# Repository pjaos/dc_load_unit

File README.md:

# DC Load Unit
I started this project with some basic requirements.

- Voltages up to 100 V
- Provide loads of up to 200W
- WiFi interface
- Web based interface providing stats and plotting capabilities

## Design
I used an ESP32 processor in the design as the main processor using  [Mongoose OS](https://mongoose-os.com/) After some investigations and prototyping I eventually settled on the schematic shown below.

From the schematic a PCB was created as shown below

Tests on completion of the load unit showed it was capable of providing a load of 280W.

- Images of the completed unit.

The green LED on the unit indicates that it is connected to the WiFi.

## Web interface
The web interface uses a tabbed pane structure as shown below.

### Main interface

- Plots
The plots tab displays the amps, volts, Watts and Temperature against time as show below.

- Load stats
The load stats page records the load in amp hours and watt hours. The top two dials show the current accumulating values and the bottom two dials show the previous values. The previous values are useful for showing the total capacity of a battery tested.

- Configuration
The configuration page details the settings for the unit as detailed below.

- Device name:

 The name that appears at the top of the web page and also in the [Yview](https://github.com/pjaos/yview) as the device provides integration into the YView network.

- Group name:

  The YView group name. See [Yview](https://github.com/pjaos/yview) for more details.

- Enable syslog

  If enabled then syslog data is sent to the source of the AYT messages (YView gateway).

- Max Plot values

  Defines the max number of points on the displayed plots.

- Max power

  This defines the maximum power the load will handle. This is limited to 280 Watts. When testing it can be useful to set this value to the max load that the device under test will deliver in order not to inadvertently overload the device under test.

- Load Shutdown Voltage

  When testing battery packs the voltage will drop as the battery looses charge. This setting allows the user to ensure the battery voltage does not drop to far possibly damaging the battery.

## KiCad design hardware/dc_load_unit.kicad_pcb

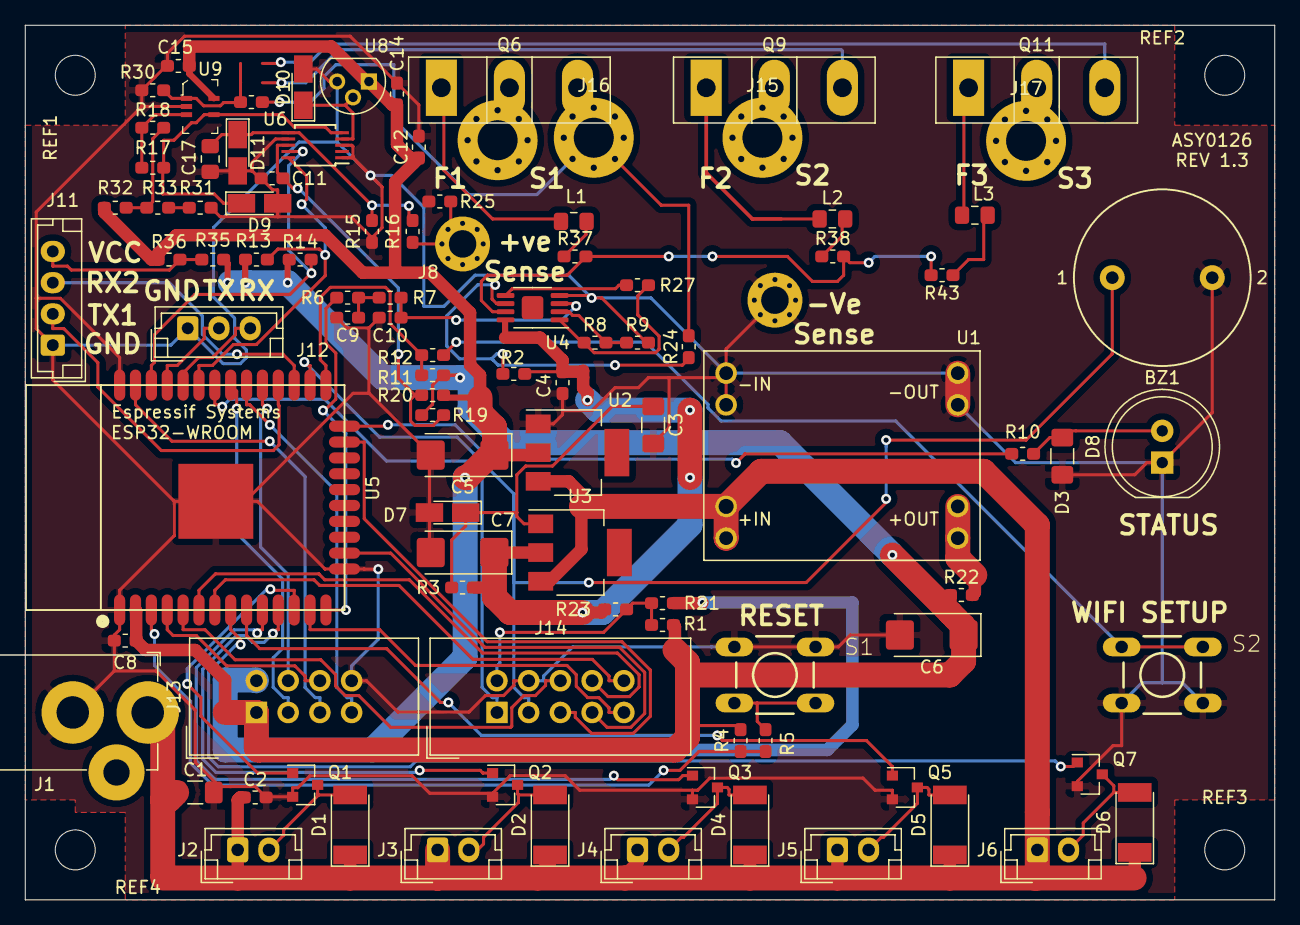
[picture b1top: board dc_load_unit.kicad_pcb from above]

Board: 2 copper layers, 100.0 x 70.0 mm, 104 parts (0 on the bottom side), 71 nets.

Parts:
BZ1: Buzzer; Buzzer_14mm_8mm_pitch
C1: 10uf 25v; C_1206_3216Metric_Pad1.42x1.75mm_HandSolder
C2, C4, C8: 0.1uf; C_0603_1608Metric_Pad1.05x0.95mm_HandSolder
C3: 10uf; C_1206_3216Metric_Pad1.42x1.75mm_HandSolder
C5, C6, C7: 22uf; CP_EIA-6032-20_AVX-F_Pad2.25x2.35mm_HandSolder
C9: 4.7nf; C_0603_1608Metric_Pad1.05x0.95mm_HandSolder
C10: 8.2nf; C_0603_1608Metric_Pad1.05x0.95mm_HandSolder
C11, C12, C14, C15: .1uf; C_0603_1608Metric_Pad1.05x0.95mm_HandSolder
C17: 470nf; C_0805_2012Metric_Pad1.15x1.40mm_HandSolder
D1, D2, D4, D5, D6: 1N4004; D_MELF
D3: LED; C_1206_3216Metric_Pad1.42x1.75mm_HandSolder
D7: 4V7; D_MicroMELF_Hadsoldering
D8: LED; LED_D8.0mm
D9, D10, D11: 3V; D_MicroMELF_Hadsoldering
J1: Conn_01x02_Male; DC_power_2.1mm_5.5mm
J2, J3, J4, J5, J6: Conn_01x02_Female; JST_EH_B2B-EH-A_1x02_P2.50mm_Vertical
J7: -Ve Sense; MountingHole_2.2mm_M2_Pad_Via
J8: +Ve Sense; MountingHole_2.2mm_M2_Pad_Via
J9: To Fuse 1; MountingHole_3.2mm_M3_Pad_Via
J11: Conn_01x04; JST_EH_B4B-EH-A_1x04_P2.50mm_Vertical
J12: Conn_01x03_Male; JST_EH_B3B-EH-A_1x03_P2.50mm_Vertical
J13: Conn_02x04_Odd_Even; IDC-Header_2x04_P2.54mm_Vertical
J14: Conn_02x05_Odd_Even; IDC-Header_2x05_P2.54mm_Vertical
J15: To Fuse 2; MountingHole_3.2mm_M3_Pad_Via
J16: 0.22R Shunt; MountingHole_3.2mm_M3_Pad_Via
J17: To Fuse 3; MountingHole_3.2mm_M3_Pad_Via
L1, L2, L3: 2.2uh; L_0805_2012Metric_Pad1.15x1.40mm_HandSolder
Q1, Q2, Q3, Q5, Q7: 2N7002; SOT-23
Q6, Q9, Q11: IXFH80N25X3; TO-247-3_Vertical
R1, R19, R22, R35: R0; R_0603_1608Metric_Pad1.05x0.95mm_HandSolder
R2: 150k; R_0603_1608Metric_Pad1.05x0.95mm_HandSolder
R3, R5, R12, R15: 470R; R_0603_1608Metric_Pad1.05x0.95mm_HandSolder
R4: 12k; R_0603_1608Metric_Pad1.05x0.95mm_HandSolder
R6, R7, R9: 10k; R_0603_1608Metric_Pad1.05x0.95mm_HandSolder
R8: 2.2k; R_0603_1608Metric_Pad1.05x0.95mm_HandSolder
R10: 681R; R_0603_1608Metric_Pad1.05x0.95mm_HandSolder
R11: 12K; R_0603_1608Metric_Pad1.05x0.95mm_HandSolder
R13, R14: 4k7; R_0603_1608Metric_Pad1.05x0.95mm_HandSolder
R16, R34: 33k; R_0603_1608Metric_Pad1.05x0.95mm_HandSolder
R17, R18, R25: 100k; R_0603_1608Metric_Pad1.05x0.95mm_HandSolder
R20, R21, R23, R32, R36: DNF; R_0603_1608Metric_Pad1.05x0.95mm_HandSolder
R24: 100R; R_0603_1608Metric_Pad1.05x0.95mm_HandSolder
R27, R33: 0R; R_0603_1608Metric_Pad1.05x0.95mm_HandSolder
R30: 68k; R_0603_1608Metric_Pad1.05x0.95mm_HandSolder
R31: 1k; R_0603_1608Metric_Pad1.05x0.95mm_HandSolder
R37, R38, R43: 2k2; R_0603_1608Metric_Pad1.05x0.95mm_HandSolder
REF1, REF2, REF3, REF4: MountingHole_3.2mm_M3
S1, S2: DTS-6; switch-tact-DTS-6
U1: DC_DC_MODULE_8_PIN; mp1584_dc_dc
U2, U3: LM1117-5V; SOT-223
U4: LM358; MSOP-8-1EP_3x3mm_P0.65mm_EP1.73x1.85mm
U5: ESP32-WROOM
U6: ADS1115IDGS; TSSOP-10_3x3mm_P0.5mm
U8: MCP9700; TO-92
U9: MCP6241UT-E_LT; SC-70-5

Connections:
3V3: C6.1, C8.1, J13.1, R1.1, R4.1, R11.2, R13.1, R14.1, R19.2, R22.1, R35.1, U5.2
5V: C5.1, C12.1, C14.1, C15.1, J13.2, R20.1, R21.1, R32.2, R36.1, U2.2, U8.1, U9.5
9V7: C4.1, C7.1, R2.1, R3.2, R23.1, U3.2, U4.8
12V: C1.1, C2.1, D1.1, D2.1, D4.1, D5.1, D6.1, J1.1, J2.1, J3.1, J4.1, J5.1, J6.1, U1.3, U1.4, U2.3, U3.3
/High_Power/+veSense: J8.1, R16.2, R25.1
/High_Power/GateDrive: R37.2, R38.2, R43.2, U4.7
/High_Power/Shunt: J16.1, Q6.3, Q9.3, Q11.3, R24.2, R34.2
CLK: J13.7, U5.30
CS: J13.4, U5.29
F1: Q1.1, U5.12
F2: Q2.1, U5.11
F3: Q3.1, U5.10
F4: Q5.1, U5.9
F5: Q7.1, U5.8
GND: BZ1.2, C1.2, C2.2, C3.2, C4.2, C5.2, C6.2, C7.2, C8.2, C9.2, C10.2, C11.2, C12.2, C14.2, C15.2, C17.2, D3.1, D7.2, D8.1, D9.2, D10.2, D11.2, J1.2, J7.1, J11.1, J12.1, J13.8, J14.4, Q1.2, Q2.2, Q3.2, Q5.2, Q7.2, R9.2, R15.2, R25.2, R30.2, R31.1, S1.1, S1.2, S2.1, S2.2, U1.1, U1.2, U1.5, U1.6, U2.1, U4.4, U5.1, U5.15, U5.38, U5.39, U6.1, U6.3, U6.7, U8.3, U9.2
INT: J13.6, U5.4
IO0: R11.1, R12.2, U5.25
MISO: J13.3, U5.31
MOSI: J13.5, U5.37
unnamed: C3.1, D7.1, R3.1, U3.1
unnamed: C9.1, R6.1, R7.2
unnamed: C10.1, R7.1, U4.3
unnamed: C11.1, R19.1, R20.2, U6.8
unnamed: C17.1, D11.1, R15.1, R16.1, U6.6
unnamed: D1.2, J2.2, Q1.3
unnamed: D2.2, J3.2, Q2.3
unnamed: D3.2, D8.2, R10.1
unnamed: D4.2, J4.2, Q3.3
unnamed: D5.2, J5.2, Q5.3
unnamed: D6.2, J6.2, Q7.3
unnamed: D9.1, R17.1, U6.5, U9.4
unnamed: D10.1, U6.4, U8.2
unnamed: J9.1, Q6.2
unnamed: J11.4, R35.2, R36.2
unnamed: J14.2, R1.2, R21.2, R23.2
unnamed: J15.1, Q9.2
unnamed: J17.1, Q11.2
unnamed: L1.1, R37.1
unnamed: L1.2, Q6.1
unnamed: L2.1, R38.1
unnamed: L2.2, Q9.1
unnamed: L3.1, R43.1
unnamed: L3.2, Q11.1
unnamed: R2.2, R24.1, U4.6
unnamed: R4.2, R5.1, U5.3
unnamed: R5.2, S1.3, S1.4
unnamed: R6.2, U5.14
unnamed: R8.2, R9.1, U4.2
unnamed: R10.2, U5.24
unnamed: R12.1, S2.3, S2.4
unnamed: R13.2, U5.33, U6.10
unnamed: R14.2, U5.36, U6.9
unnamed: R17.2, R18.1, U9.3
unnamed: R18.2, R32.1, R33.2
unnamed: R22.2, U1.7, U1.8
unnamed: R27.1, U4.5
unnamed: R8.1, R27.2, U4.1
unnamed: R30.1, R34.1, U9.1
unnamed: R31.2, R33.1
RXD: J12.3, U5.34
RXD2: J11.3, U5.27
SP1: J14.1, U5.32
SP2: BZ1.1, J14.3, U5.26
SP3: J14.5, U5.23
SP4: J14.7, U5.16
SP5: J14.9, U5.13
SP6: J14.10, U5.7
SP7: J14.8, U5.6
SP8: J14.6, U5.5
TXD: J12.2, U5.35
TXD2: J11.2, U5.28

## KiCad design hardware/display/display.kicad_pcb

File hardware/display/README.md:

# Display board
This was a side project of an LCD display board that could be used with the
dc load unit to control it. However the web interface is my preferred
GUI interface and therefore I did not develop this board any further.

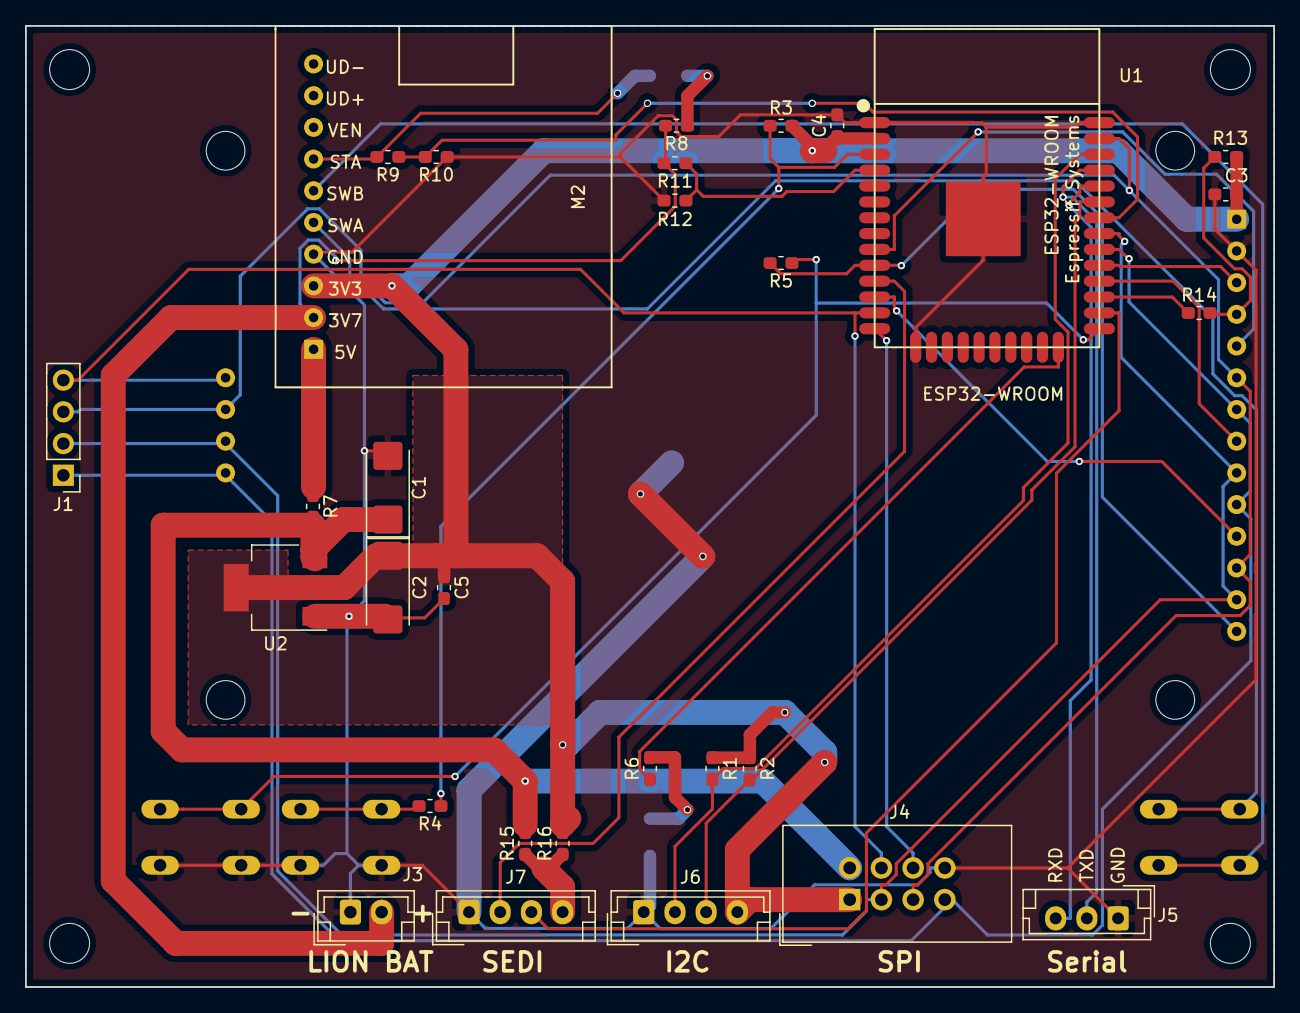
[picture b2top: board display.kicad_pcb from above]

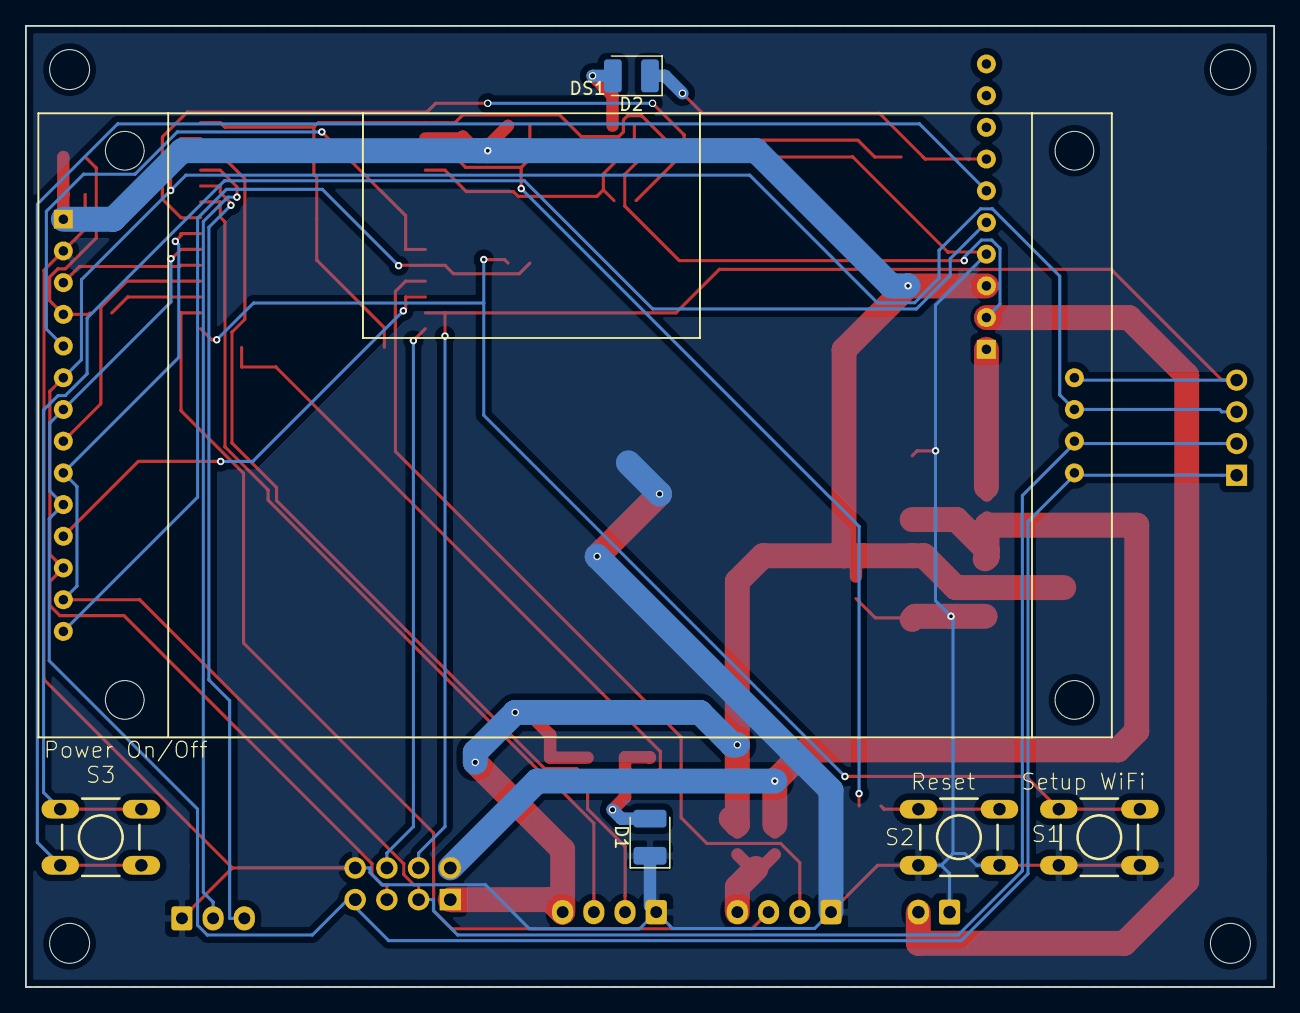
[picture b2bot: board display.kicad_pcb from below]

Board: 2 copper layers, 100.0 x 77.0 mm, 40 parts (6 on the bottom side), 35 nets.

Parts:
C1, C2: DNF; CP_EIA-6032-20_AVX-F_Pad2.25x2.35mm_HandSolder
C3, C4: 0.1uf; C_0603_1608Metric_Pad1.05x0.95mm_HandSolder
C5: DNF; C_0603_1608Metric_Pad1.05x0.95mm_HandSolder
D1, D2: LED; LED_1210_3225Metric_Pad1.42x2.65mm_HandSolder
DS1: display_2.8inch_ili9341; LCD_2.8_INCH_MSP2807
J1: Conn_01x04_Male; PinHeader_1x04_P2.54mm_Vertical
J3: Lion Bat; JST_EH_B2B-EH-A_1x02_P2.50mm_Vertical
J4: SPI; IDC-Header_2x04_P2.54mm_Vertical
J5: Serial; JST_EH_B3B-EH-A_1x03_P2.50mm_Vertical
J6: I2C; JST_EH_B4B-EH-A_1x04_P2.50mm_Vertical
J7: SEDI; JST_EH_B4B-EH-A_1x04_P2.50mm_Vertical
M2: usb_bat_pwr_module; USB_BAT_PWR_MODULE
MH1, MH2, MH3, MH4: MountingHole_3.2mm_M3
R1, R2: 1K; R_0603_1608Metric_Pad1.05x0.95mm_HandSolder
R3: 10K; R_0603_1608Metric_Pad1.05x0.95mm_HandSolder
R4, R6, R8: 470R; R_0603_1608Metric_Pad1.05x0.95mm_HandSolder
R5, R7: DNF; R_0603_1608Metric_Pad1.05x0.95mm_HandSolder
R9, R11: 68K; R_0603_1608Metric_Pad1.05x0.95mm_HandSolder
R10, R12: 100K; R_0603_1608Metric_Pad1.05x0.95mm_HandSolder
R13: 47K; R_0603_1608Metric_Pad1.05x0.95mm_HandSolder
R14, R15, R16: 0R; R_0603_1608Metric_Pad1.05x0.95mm_HandSolder
S1: Setup WiFi; switch-tact-DTS-6
S2: Reset; switch-tact-DTS-6
S3: Power On/Off; switch-tact-DTS-6
U1: ESP32-WROOM
U2: LM1117-3V3; SOT-223-3_TabPin2

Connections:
3V3: C2.1, C3.1, C4.1, C5.1, DS1.1, J4.1, J6.4, M2.3, R1.1, R2.1, R3.2, R13.1, R16.2, U1.2, U2.2
5V: C1.1, J4.2, R7.2, R15.2, U2.3
/5VBAT: M2.1, R7.1
/BAT+: J3.2, M2.2, R8.2, R11.2
CS0: DS1.3, U1.29
CS1: DS1.11, U1.12
CS2: DS1.15, J1.4, J4.4, U1.13
DRX: J7.3, U1.26
DTX: J7.2, U1.11
GND: C1.2, C2.2, C3.2, C4.2, C5.2, D1.1, DS1.2, J3.1, J4.8, J5.1, J6.1, J7.1, M2.4, R10.1, R12.1, S1.1, S1.2, S2.1, S2.2, U1.1, U1.15, U1.38, U1.39, U2.1
INT: J4.6, U1.14
MISO: DS1.9, DS1.13, DS1.17, J1.2, J4.3, U1.31
MOSI: DS1.6, DS1.12, DS1.16, J1.3, J4.5, U1.37
unnamed: D1.2, R6.2
unnamed: D2.1, M2.7, R9.2
unnamed: D2.2, R8.1
unnamed: DS1.4, R13.2, R14.2
unnamed: DS1.5, U1.9
unnamed: DS1.8, U1.28
unnamed: DS1.14, R5.2, U1.10
unnamed: J7.4, R15.1, R16.1
unnamed: M2.5, S3.3, S3.4
unnamed: M2.6, S3.1, S3.2
unnamed: R3.1, R4.1, U1.3
unnamed: R4.2, S2.3, S2.4
unnamed: R5.1, S1.3, S1.4, U1.25
unnamed: R6.1, U1.24
unnamed: R9.1, R10.2, U1.32
unnamed: R11.1, R12.2, U1.4
unnamed: R14.1, U1.27
RXD: J5.3, U1.34
SCK: DS1.7, DS1.10, DS1.18, J1.1, J4.7, U1.30
SCL: J6.3, R2.2, U1.33
SDA: J6.2, R1.2, U1.36
TXD: J5.2, U1.35

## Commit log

2021-01-07 Add a file to ignore files we don't want in git
2021-01-07 Initial commit of the dc load hardware and software.
2021-01-07 Add eclipse .project file.
2021-01-09 Move the logging to a separate file.
2021-01-09 - Add log level to the log_msg function. - Add RPC to reset temp alarms - Add RPC to set debug level. Sys.SetDebug exists but takes three arguments.
2021-01-16 Config can be read and saved from the web page now.
2021-01-16 Moved to sofwtare folder.
2021-01-16 Add the guage javascript to the repo.
2021-01-17 Add updated examples of REST interface access.
2021-01-17 Dials are now working. Plots are not.
2021-01-20 - Added 2.2 uh inductors to MOSFET gates to stop parasitic OSC - Added 470nf cap accross R15.
2021-01-20 Added todo list.
2021-01-20 Changed Watts text to Power.
2021-01-20 - Destroy the old guage if a new one is created when the MAX value is reached. - Reinstate plotting data.
2021-01-20 Set default plot time period to 60 seconds.
2021-01-20 Make fan API simpler.
2021-01-20 Use new fan API and improve the load off definition.
2021-01-23 Add eclipse project files that allow .c and .h indexing.
2021-01-26 - initial implementation of PID load control. - Add fan count dial to monitor cooling.
2021-01-26 Reverse Plots and Dials tabs in web interface.
2021-01-26 Allow the user to set the target amps from the web interface.
2021-01-26 Remove target watts field from web interface.
2021-01-26 Change web interface current input field label from 'Current (Amps)' to 'Target Current (Amps)'
2021-01-26 Set plot colour to green.
2021-01-26 Remove req from notes now its done.
2021-01-26 Remove PJA debug text from src.
2021-01-26 Add rpcs for calibrating amps and volts.
2021-01-26 - Set the default voltage and current calibration values. - Constantly adjust the amps rather than settling in a band.
2021-01-26 Update TODO field
    Please enter the commit message for your changes. Lines starting
2021-01-26 - Fixed bug in fan status in web interface. Dial shows off fan still running as temperature is dropping.
2021-01-27 Set load if user presses enter in the target amps field.
2021-01-27 Drop the dials panel and change the look and feel.
2021-01-27 Add load off button that resets the load to 0.
2021-01-29 Fix bug 'DC load unit does not appear in ydev list.'
2021-01-30 Add latest version (2.1.7) of the gauge.
2021-01-30 Fix gauges getting corrupted
2021-01-31 Fix issues with the dials causing browser crashes and not working correctly.
2021-01-31 Change default unit name.
2021-01-31 Update TODO list.
2021-01-31 Add rpc handler to reboot the unit.
2021-01-31 Updtae TODO list.
2021-01-31 Remove commented out debug code.
2021-01-31 Add RPC to set the min load voltage. When the load voltage drops to this level the load turns off.
2021-02-01 Remove JS error.
2021-02-01 Add load shutdown voltage options. When the voltage reaches this voltage the load automatically turns off. Useful when testing batteries.
2021-02-02 Tidy the code a bit.
2021-02-02 Save the config if enter is pressed in any of the text fields on the config tab.
2021-02-02 Limit the minimum voltage so that the voltage dial does not move around below 30 MV.
2021-02-02 Change the plo points config field text and tool text.
2021-02-02 Change log messages from debug to info level no defaulkt debug option is off.
2021-02-03 Report a temp alarm to the user. When the temp of the heatsink reaches a maximuum (79C) the load is shutdown and this is reported to the user via a dialog box which blocks access to the GUI until the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
2021-02-04 Add record of the time that the load is on for. This is not presented on the web interface yet.
2021-02-04 Correct error where dials appeared on plots tab.
2021-02-05 Add tab to show load stats, AMp hours etc.
2021-02-06 Add the load on time to the Load Stats tab in the legend of the fieldset.
2021-02-06 Correct the style of the tab to use a css class that exists.
2021-02-06 Reinstate tablinks class as it's used un the Javascript to select the current tab.
2021-02-06 Add a favicon.ico to the web server.
2021-02-06 Add a min low voltage alarm that is reported in the web browser as a dialog that appears. When the user clicks the OK button in the dialog the alarm is reset. This is only reported if the load is on.
2021-02-06 R16 changed from 47k to 33k to get better resolution on the ADC.
2021-02-06 - If a voltage of 200V is detected on the DC load terminal the load is shiut down. - Add a MAX load voltage warning to the web GUI.
2021-02-06 If a voltage of 200V is detected on the DC load terminal the load is shiut down.
2021-03-06 Update schematic and PCB to use shunt resistors to measure throughtput and add FET protection for over current.
2021-03-06 Add support for warning buzzer on dc load unit.
2021-04-22 C1 changed from DNF to 10uf C2 changed from DNF to 22uf R16 changed form 0R to DNF
2021-04-22 R10 330R -> 681R as LED is too bright R25 3.3k -> 2.2k to change low end gate voltage
2021-05-02 Rev 1.3 single shunt with op amp drive change to make gate drive voltage directly related to load current.
2021-05-02 Add jbcl rev 1.3 gerber package.
2021-05-02 Add high power schematic sheet.
2021-05-03 Add document to detail how to call the REST interface methods on the dc load unit.
2021-05-03 Add Freecad backup files to the list of ignored files.
2021-05-03 Add ability to set a limit on the max power the load will handle. This triggers a warning if the user enters a current value that breaks this limit.
2021-05-03 Add a TODO list to capture outstanding issues and future improvements.
2021-05-03 Correct #define to #ifdef
2021-05-03 Limit the MAX power of the DC load to 280 Watts.
2021-05-13 Provide an overview documentation page for the project.
2021-05-30 Add readme file with a short description of the display hardware.
2021-05-30 Ignore archive folders
2021-09-27 Add details of the PCB.
2024-03-03 Add a 10uf 250v capacitor to the input sense lead to ensure we don't get over voltage errors when the sense lead is touched by human hand.
